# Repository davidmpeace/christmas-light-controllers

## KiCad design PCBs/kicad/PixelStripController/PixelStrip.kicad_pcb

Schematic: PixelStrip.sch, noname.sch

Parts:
C1, C2, C3, C4: .1uF
D1: IN5239
D2: IN5229
D3: LED
ISP1: ISP
J1, J2: 215877-1
JP1: JUMPER
P1: PWR
P2: PIXEL_OUT
R1: 120
R2, R5: 27K
R3, R4: 1K
R6: 680
TP1, TP2, TP3, TP4: TESTPOINT
U1, U2: SN65LBC176AP
U3: ATMEGA328P
U4: 18.432_MHZ

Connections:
+5V: C1.2, C2.2, C3.2, C4.1, ISP1.2 (VCC), P1.1 (+5V), P2.1 (+5V), R2.1, R6.2, U1.8 (Vcc), U2.2 (~RE), U2.3 (DE), U2.8 (Vcc), U3.7, U3.20, U3.21, U4.8 (VDD)
GND: C1.1, C2.1, C3.1, C4.2, D2.2 (K), D3.2 (K), ISP1.6 (GND), J1.1, J1.2, J1.6, J2.1, J2.2, J2.6, P1.2 (GND), P2.2 (GND), R5.2, U1.2 (~RE), U1.3 (DE), U1.5 (GND), U2.5 (GND), U3.8, U3.22, U4.4 (GND)
unnamed: ISP1.1 (MISO), U3.18
unnamed: ISP1.5 (RESET), U3.1
unnamed: U3.9, U4.5 (OUT)
unnamed: U2.4 (D), U3.3
unnamed: U1.1 (R), U3.2
unnamed: JP1.1, R1.2
unnamed: R2.2, R3.1, TP3.1, U1.6 (A)
unnamed: D1.1 (A), D2.1 (A)
unnamed: J1.3, J2.3
unnamed: J2.5, TP1.1, U2.6 (A)
unnamed: D1.2 (K), R4.2, R5.1, TP4.1, U1.7 (B)
unnamed: P2.3 (DATA), U3.15
unnamed: J2.4, TP2.1, U2.7 (B)
unnamed: ISP1.4 (MOSI), U3.17
unnamed: ISP1.3 (SCK), U3.19
unnamed: D3.1 (A), R6.1
unnamed: J1.4, JP1.2, R4.1
unnamed: J1.5, R1.1, R3.2
unnamed: J1.7, J1.8, J2.7, J2.8

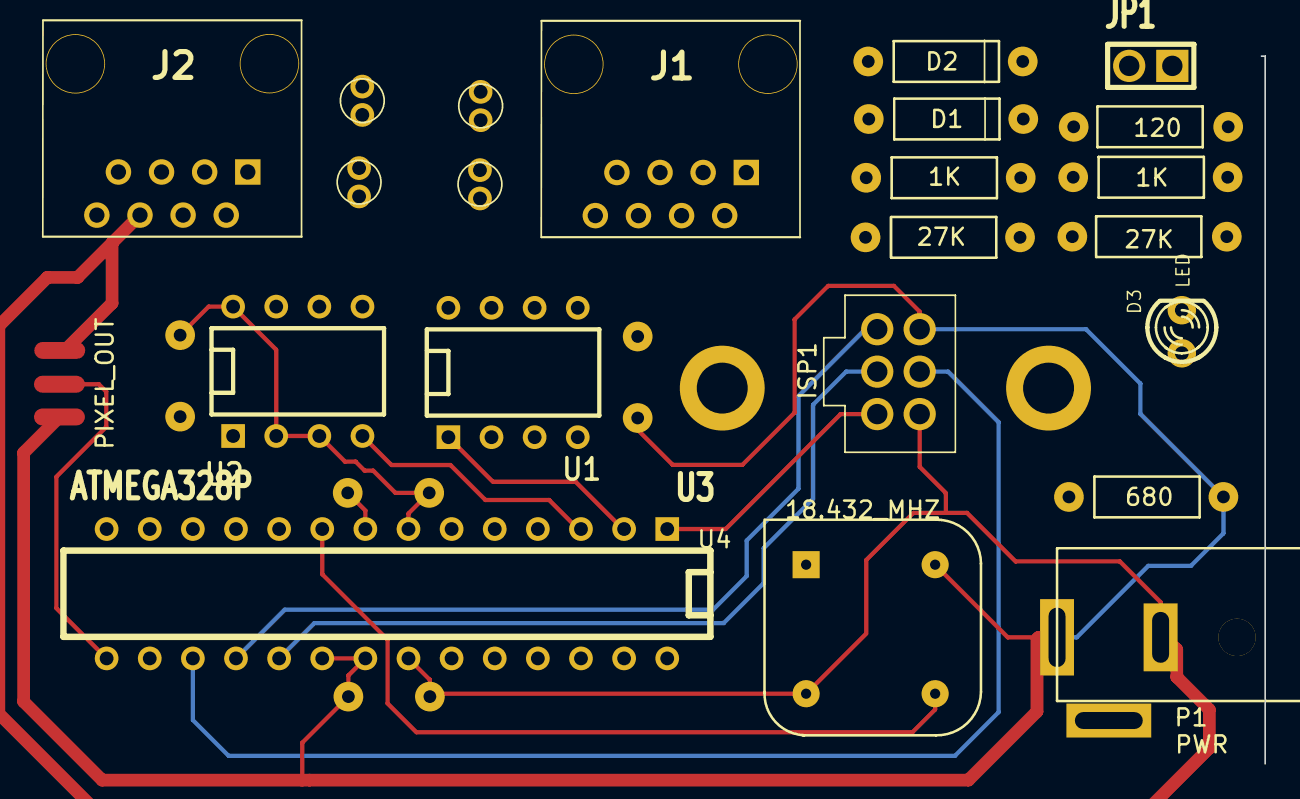
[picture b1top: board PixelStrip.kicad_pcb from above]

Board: 2 copper layers, 27 parts (0 on the bottom side), 21 nets.

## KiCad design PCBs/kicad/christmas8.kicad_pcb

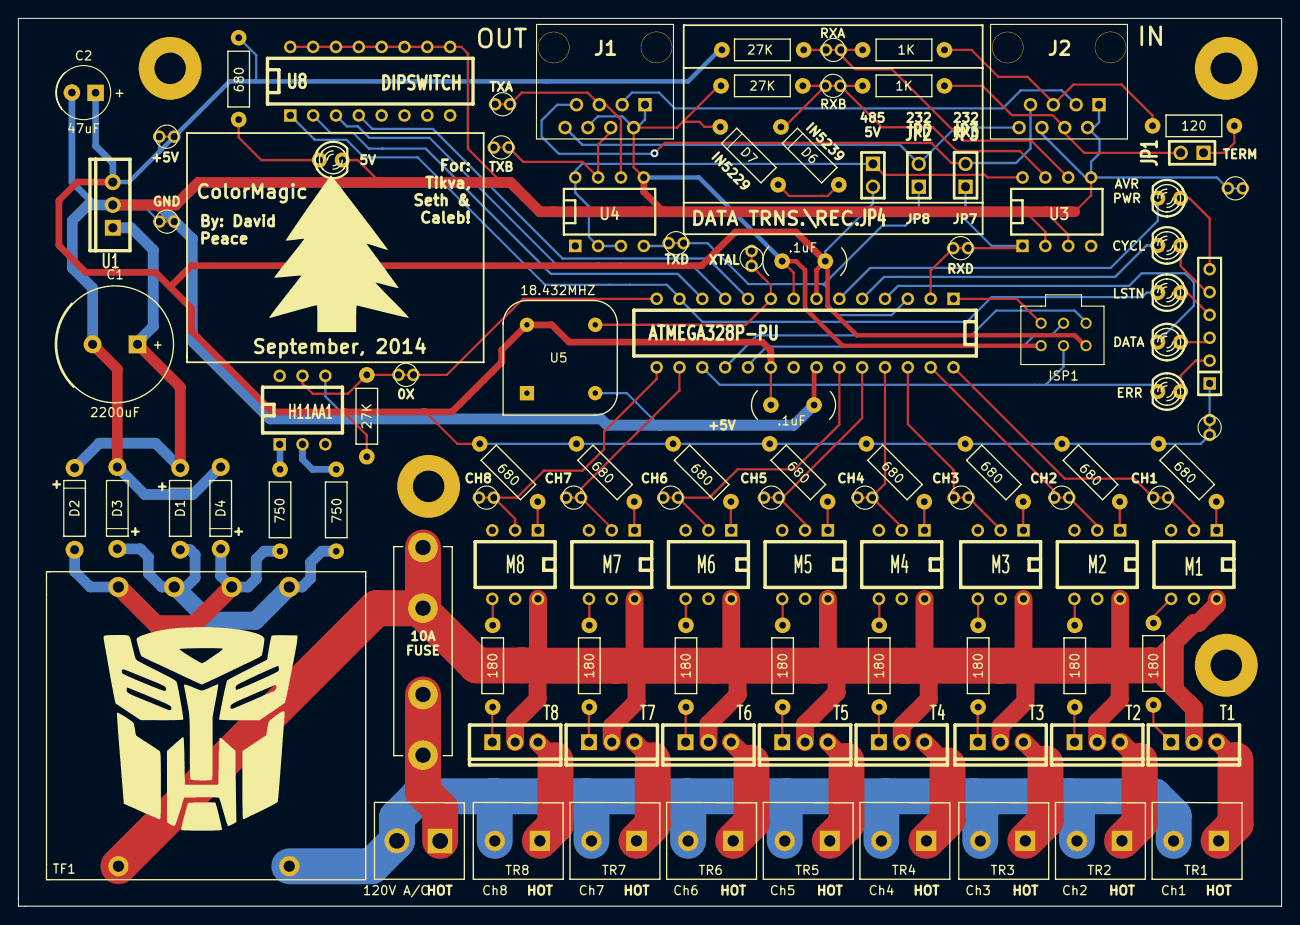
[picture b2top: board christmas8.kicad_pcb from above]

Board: 2 copper layers, 140.5 x 98.8 mm, 118 parts (0 on the bottom side), 83 nets.

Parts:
 : test_point
 #2,  #3,  #4,  #5,  #6,  #7,  #8,  #9,  #10,  #11,  #12,  #13,  #14,  #15: test_point
C1: 2200uF; 16V_2200uF
C2: 47uF
C3, C4: .1uF
D1, D2, D3, D4: 1N5817; Diode_Wider
D5: PWR; LED-3MM
D6: IN5239; Diode
D7: IN5229; Diode
D8, D9, D10, D11, D12: LED; LED-3MM
F1: 10A_FUSE
ISP1: ISP
J1: 215877-1 (OUT); RJ45_8_SHORT
J2: 215877-1 (IN); RJ45_8_SHORT
JP1, JP2, JP3, JP4: JUMPER
M1, M2, M3, M4, M5, M6, M7, M8: MOC3023; DIP-6__300
R1, R101, R102, R103, R104, R105, R106, R107, R108: 680; Resisitor
R2, R3: 750; Resisitor
R4, R453, R455: 27K; Resisitor
R201, R202, R203, R204, R205, R206, R207, R208: 180; Resisitor
R451: 120; Resisitor
R452, R454: 1K; Resisitor
RN1: RESISTOR_NET; r_pack5
T1, T2, T3, T4, T5, T6, T7, T8: BTA06; TO220_VERT
TF1: 3FS-312; Transformer
TP1, TP2, TP3, TP4, TP5, TP6, TP7, TP8, TP9, TP10, TP11, TP12, TP13, TP14, TP15, TP16, TP17, TP19, TP20, TP21: TESTPOINT; TESTPOINT-CIRCLE
TR0: 120V A/C; 120Terminal
TR1: Ch1; Terminal
TR2: Ch2; Terminal
TR3: Ch3; Terminal
TR4: Ch4; Terminal
TR5: Ch5; Terminal
TR6: Ch6; Terminal
TR7: Ch7; Terminal
TR8: Ch8; Terminal
U1: LF50CV; TO220_VERT_REG
U2: H11AA1; DIP-6__300
U3, U4: SN65LBC176AP; DIP-8__300
U5: 18.432MHZ; 18.432MHz
U7: ATMEGA328P-PU; DIP-28__300
U8: DIPSWITCH; DIP-16__300

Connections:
+5V: C2.1, C3.2, C4.1, ISP1.2, JP4.2, R1.1, R4.2, R101.2, R102.2, R103.2, R104.2, R105.2, R106.2, R107.2, R108.2, R453.2, RN1.1, TP1.1, TP13.1, U1.3, U7.7, U7.20
GND: C1.2, C2.2, C3.1, C4.2, D3.1, D4.1, D5.2, D7.2, ISP1.6, J1.1, J1.2, J1.6, J2.1, J2.2, J2.6, R455.1, TP2.1, TP12.1, U1.2, U2.4, U3.2, U3.3, U3.5, U4.5, U7.8, U7.22, U8.9, U8.10, U8.11, U8.12, U8.13, U8.14, U8.15, U8.16
unnamed: J1.8, J2.8, JP2.2
unnamed: D9.2, U7.4
unnamed: D12.2, U7.6
unnamed: D8.1, RN1.2
unnamed: D9.1, RN1.3
unnamed: D10.1, RN1.4
unnamed: D11.1, RN1.5
unnamed: D12.1, RN1.6
unnamed: C1.1, D1.2, D2.2, U1.1
unnamed: T5.2, TR5.1
unnamed: T6.2, TR6.1
unnamed: T7.2, TR7.1
unnamed: T4.2, TR4.1
unnamed: F1.2, M1.6, M2.6, M3.6, M4.6, M5.6, M6.6, M7.6, M8.6, T1.3, T2.3, T3.3, T4.3, T5.3, T6.3, T7.3, T8.3, TF1.1
unnamed: F1.1, TR0.1
unnamed: R202.1, T2.1
unnamed: R204.1, T4.1
unnamed: M4.4, R204.2
unnamed: R203.1, T3.1
unnamed: M3.4, R203.2
unnamed: M2.4, R202.2
unnamed: R201.1, T1.1
unnamed: M1.4, R201.2
unnamed: T8.2, TR8.1
unnamed: T2.2, TR2.1
unnamed: T3.2, TR3.1
unnamed: D6.1, D7.1
unnamed: JP1.1, R451.2
unnamed: TF1.4, TR0.2, TR1.2, TR2.2, TR3.2, TR4.2, TR5.2, TR6.2, TR7.2, TR8.2
unnamed: T1.2, TR1.1
unnamed: R2.2, U2.1
unnamed: J1.4, TP4.1, U4.7
unnamed: J2.5, R451.1, R452.2
unnamed: J2.4, JP1.2, R454.2
unnamed: M2.2, TP14.1, U7.27
unnamed: TP11.1, U7.9
unnamed: M3.2, TP15.1, U7.26
unnamed: M4.2, TP16.1, U7.25
unnamed: M5.2, TP17.1, U7.24
unnamed: M6.2, TP19.1, U7.23
unnamed: J1.5, TP3.1, U4.6
unnamed: R452.1, R453.1, TP6.1, U3.6
unnamed: D6.2, R454.1, R455.2, TP7.1, U3.7
unnamed: R4.1, TP5.1, U2.5, U7.14
unnamed: M7.2, TP20.1, U7.16
unnamed: M8.2, TP21.1, U7.15
unnamed: ISP1.1, U7.18
unnamed: D8.2, ISP1.4, U7.17
unnamed: ISP1.3, U7.19
unnamed: D11.2, U7.5
unnamed: ISP1.5, U7.1
unnamed: U7.12, U8.2
unnamed: U7.10, U8.4
unnamed: U7.11, U8.3
unnamed: JP3.1, TP9.1, U3.1, U7.2
unnamed: JP4.1, U3.8, U4.2, U4.3, U4.8
unnamed: D10.2, U7.13, U8.1
unnamed: J1.7, J2.7, JP3.2
unnamed: JP2.1, TP8.1, U4.4, U7.3
unnamed: R3.2, U2.2
unnamed: D5.1, R1.2
unnamed: J1.3, J2.3
unnamed: M1.1, R101.1
unnamed: M2.1, R102.1
unnamed: M7.1, R107.1
unnamed: M8.1, R108.1
unnamed: R208.1, T8.1
unnamed: M8.4, R208.2
unnamed: R207.1, T7.1
unnamed: M7.4, R207.2
unnamed: R206.1, T6.1
unnamed: R205.1, T5.1
unnamed: M3.1, R103.1
unnamed: M4.1, R104.1
unnamed: M5.1, R105.1
unnamed: M5.4, R205.2
unnamed: M6.1, R106.1
unnamed: M6.4, R206.2
unnamed: M1.2, TP10.1, U7.28
unnamed: D2.1, D4.2, R2.1, TF1.5, TF1.7
unnamed: D1.1, D3.2, R3.1, TF1.6, TF1.8
